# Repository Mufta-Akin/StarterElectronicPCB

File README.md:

# StarterElectronicPCB
Thia is a small 5 volt regulator circuit to demonstrate PCB layout knowledge.

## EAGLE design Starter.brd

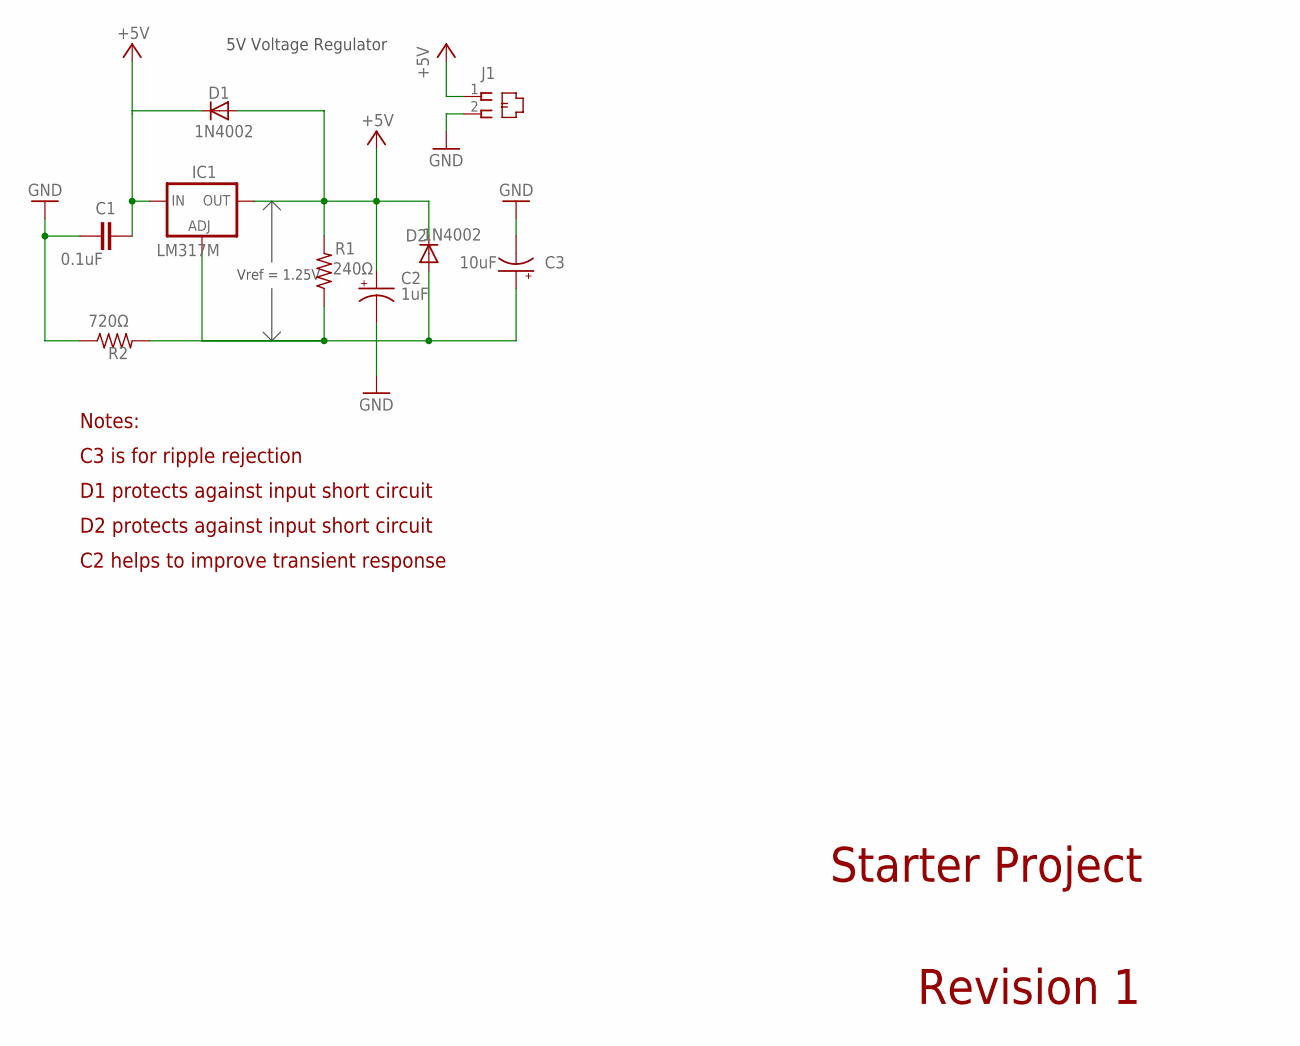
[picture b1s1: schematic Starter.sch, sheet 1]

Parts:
C1: 0.1uF; C075-052X106
C2: 1uF; 085CS_1AR
C3: 10uF; 085CS_1AR
D1, D2: 1N4002; DO41-10
IC1: LM317MBSTT3; SOT223; PARTNUMBER LM317M
J1: 520250-1
R1: 240Ω; M0805
R2: 720Ω; M0805

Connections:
+5V: C1.1, C2.+, D1.A, D1.C, D2.C, IC1.3 (IN), IC1.4 (OUT), J1.1, R1.2
GND: C1.2, C2.-, C3.-, J1.2, R2.1
unnamed: C3.+, D2.A, IC1.1 (ADJ), R1.1, R2.2

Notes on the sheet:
Starter Project
Revision 1
5V Voltage Regulator
Vref = 1.25V
Notes:
C3 is for ripple rejection
D1 protects against input short circuit
D2 protects against input short circuit
C2 helps to improve transient response

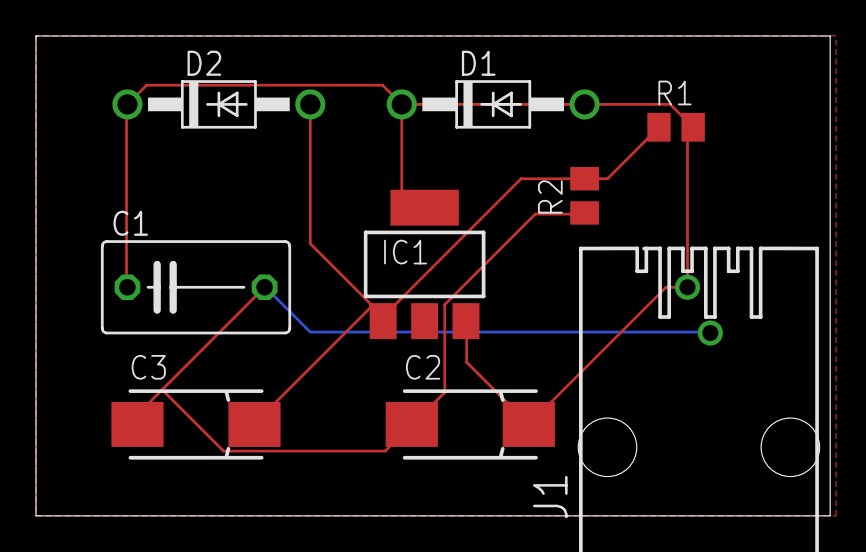
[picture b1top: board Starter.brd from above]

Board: 2 copper layers, 44.1 x 26.7 mm, 9 parts (0 on the bottom side), 3 nets.

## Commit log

2021-08-22 first components
2021-08-22 revised components
2021-08-22 Nets connected
2021-08-22 Board added
2021-08-22 Connector added
2021-08-22 Manual Routing
2021-08-22 Auto routed
2021-08-22 Copper poured
2021-08-22 CamOutput generated
